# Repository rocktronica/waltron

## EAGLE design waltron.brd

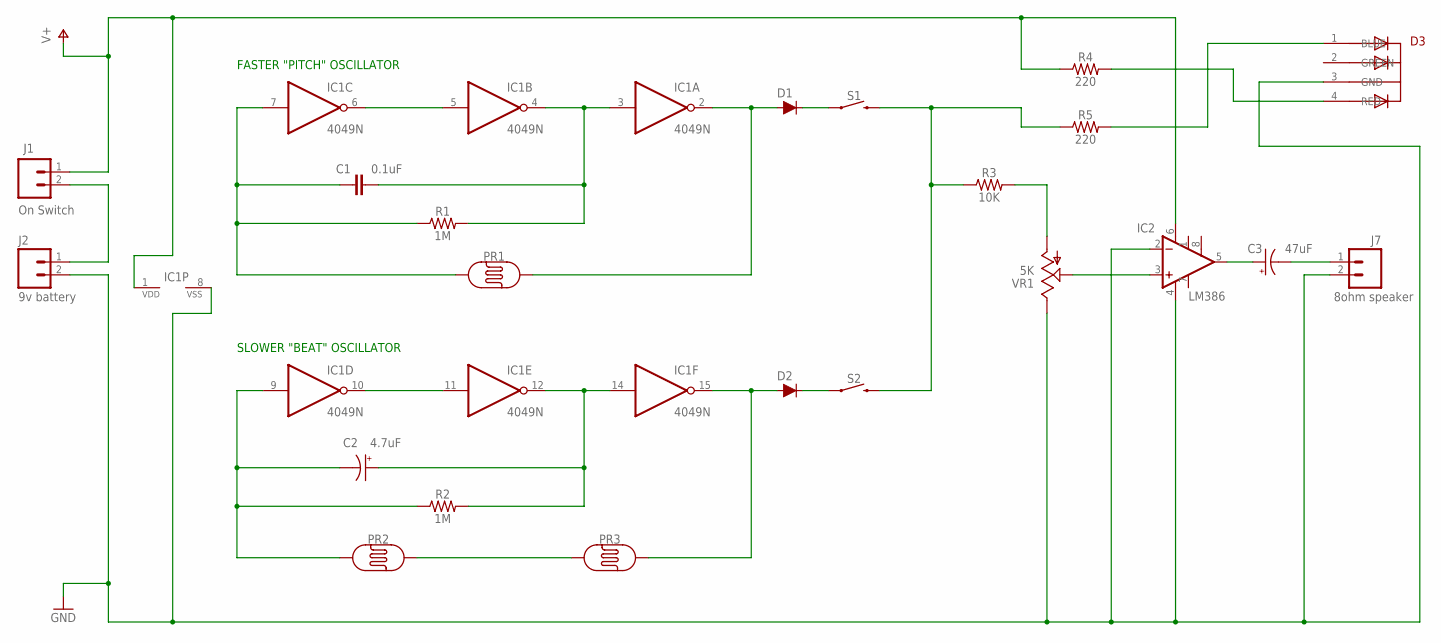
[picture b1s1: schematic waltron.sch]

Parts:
C1: 0.1uF; CAP-PTH-SMALL-KIT
C2: 4.7uF; CPOL-RADIAL-2.5MM-5MM
C3: 47uF; CPOL-RADIAL-2.5MM-5MM
D1, D2: DIODE-1N4148
D3: 5MMRGBLED; LED5MMRGB
IC1: 4049N; DIL16
IC2: LM386; DIP08
J1: On Switch; 1X02
J2: 9v battery; 1X02
J7: 8ohm speaker; 1X02
PR1, PR2, PR3: PHOTOCELLPTH-KIT; PHOTOCELL-KIT
R1, R2: 1M; AXIAL-0.3
R3: 10K; AXIAL-0.3
R4, R5: 220; AXIAL-0.3
S1, S2: MOMENTARY-SWITCH-SPST-PTH-6.0MM; TACTILE_SWITCH_PTH_6.0MM
VR1: 5K; TRIM_POT

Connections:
GND: D3.3 (GND), IC1.8 (VSS), IC2.2 (-IN), IC2.4 (V-), J2.2, J7.2, VR1.2 (E)
unnamed: IC1.5 (I), IC1.6 (O)
unnamed: C1.2, IC1.3 (I), IC1.4 (O), R1.P$2 (2)
unnamed: C1.1, IC1.7 (I), PR1.1, R1.P$1 (1)
unnamed: D1.A, IC1.2 (O), PR1.2
unnamed: C2.2 (-), IC1.9 (I), PR2.1, R2.P$1 (1)
unnamed: IC1.10 (O), IC1.11 (I)
unnamed: C2.1 (+), IC1.12 (O), IC1.14 (I), R2.P$2 (2)
unnamed: D2.A, IC1.15 (O), PR3.2
unnamed: D1.C, S1.1
unnamed: PR2.2, PR3.1
unnamed: D2.C, S2.1
unnamed: R3.P$1 (1), R5.P$1 (1), S1.3 (2), S2.3 (2)
unnamed: R3.P$2 (2), VR1.3 (A)
unnamed: C3.1 (+), IC2.5 (OUT)
unnamed: C3.2 (-), J7.1
unnamed: IC2.3 (+IN), VR1.1 (S)
unnamed: D3.1 (BLUE), R5.P$2 (2)
unnamed: D3.4 (RED), R4.P$2 (2)
unnamed: J1.2, J2.1
V+: IC1.1 (VDD), IC2.6 (V+), J1.1, R4.P$1 (1)

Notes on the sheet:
SLOWER "BEAT" OSCILLATOR
FASTER "PITCH" OSCILLATOR

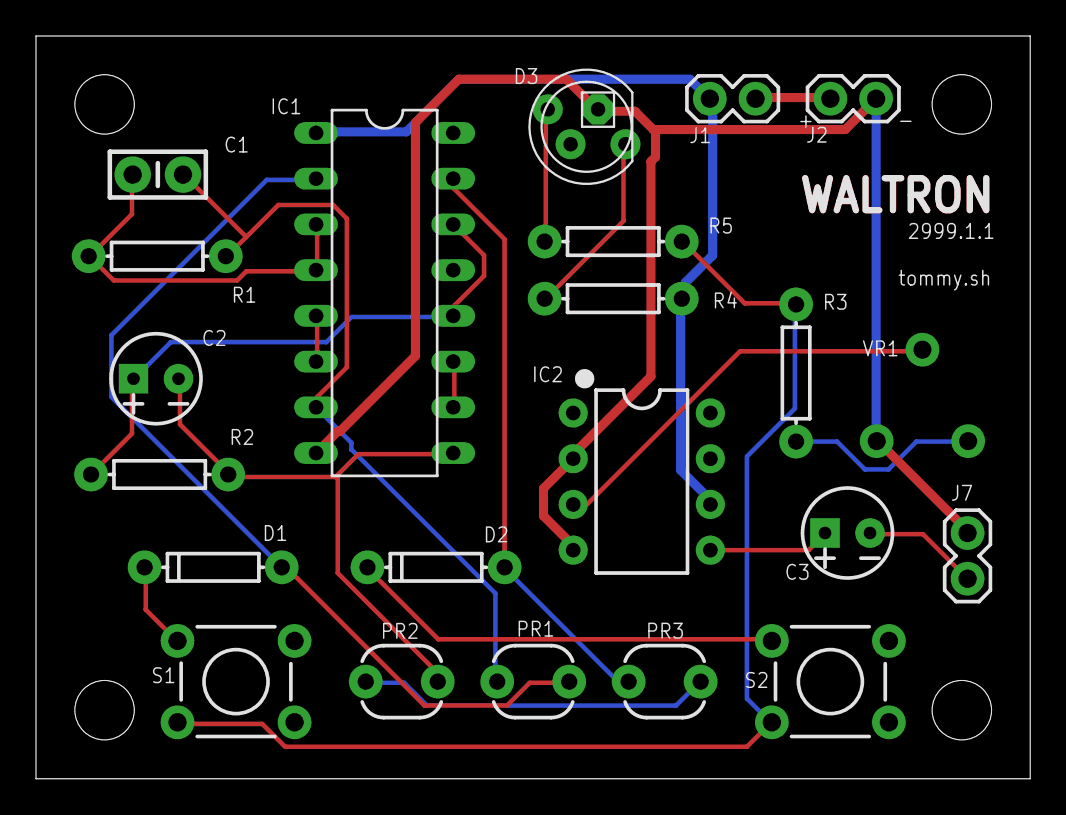
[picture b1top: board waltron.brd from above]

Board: 2 copper layers, 55.2 x 41.3 mm, 22 parts (1 on the bottom side), 21 nets.

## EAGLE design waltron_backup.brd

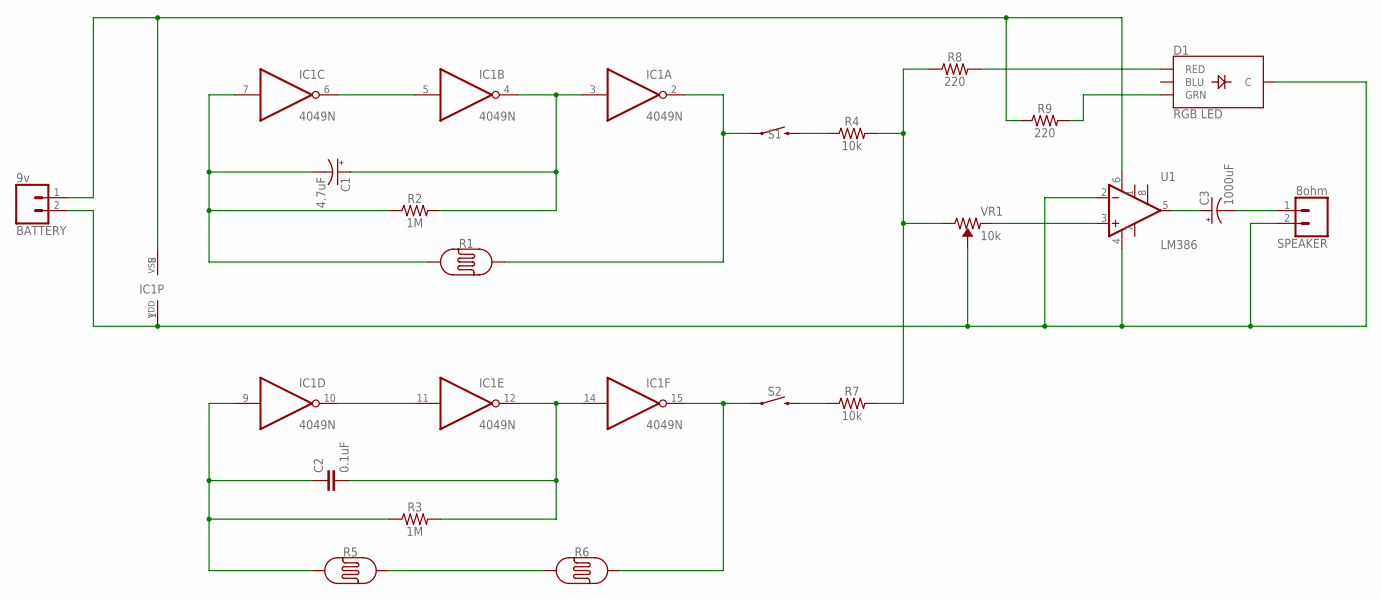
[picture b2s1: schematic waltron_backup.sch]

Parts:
BATTERY: 9v; 1X02
C1: 4.7uF; CPOL-RADIAL-2.5MM-5MM
C2: 0.1uF; CAP-PTH-SMALL-KIT
C3: 1000uF; CPOL-RADIAL-2.5MM-5MM
D1: RGB LED; LED-RGB-THRU
IC1: 4049N; DIL16
R1, R5, R6: PHOTOCELLPTH-KIT; PHOTOCELL-KIT
R2, R3: 1M; AXIAL-0.1
R4, R7: 10k; AXIAL-0.1
R8, R9: 220; AXIAL-0.1
S1, S2: MOMENTARY-SWITCH-SPST-PTH-6.0MM; TACTILE_SWITCH_PTH_6.0MM
SPEAKER: 8ohm; 1X02
U1: LM386; DIP08
VR1: 10k; TRIMPOT-PTH-3386U

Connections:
unnamed: IC1.5 (I), IC1.6 (O)
unnamed: C1.1 (+), IC1.3 (I), IC1.4 (O), R2.P$2 (2)
unnamed: C1.2 (-), IC1.7 (I), R1.1, R2.P$1 (1)
unnamed: IC1.2 (O), R1.2, S1.1
unnamed: C2.1, IC1.9 (I), R3.P$1 (1), R5.1
unnamed: IC1.10 (O), IC1.11 (I)
unnamed: C2.2, IC1.12 (O), IC1.14 (I), R3.P$2 (2)
unnamed: IC1.15 (O), R6.2, S2.1
unnamed: R4.P$1 (1), S1.3 (2)
unnamed: R5.2, R6.1
unnamed: R7.P$1 (1), S2.3 (2)
unnamed: R4.P$2 (2), R7.P$2 (2), R8.P$1 (1), VR1.3 (CW)
unnamed: U1.3 (+IN), VR1.1 (CCW)
unnamed: C3.1 (+), U1.5 (OUT)
unnamed: C3.2 (-), SPEAKER.1
unnamed: D1.1 (RED), R8.P$2 (2)
unnamed: D1.3 (GRN), R9.P$2 (2)
VDD: BATTERY.2, D1.2 (C), IC1.1 (VDD), SPEAKER.2, U1.2 (-IN), U1.4 (V-), VR1.2 (WIPER)
VSS: BATTERY.1, IC1.8 (VSS), R9.P$1 (1), U1.6 (V+)

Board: 2 copper layers, 20 parts (0 on the bottom side), 19 nets, no tracks yet.

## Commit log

2017-03-21 Belated init
2017-03-21 Remove lock
2017-03-21 Fix miswired volume pot
2017-03-21 Provide ground to D3
2017-03-21 Add battery lead labels
2017-03-21 Lay resistors flat, rip up routes
2017-03-22 Switch out trimmer
2017-03-22 Rearrange components, iterate version to 2999.1
2017-03-23 More rearrangement, separating out optional on-board parts
2017-03-24 New layout, routed
2017-03-24 Fix labels
2017-03-24 Re-routed, missing D3 GND
2017-03-24 Replaced D3 component w/ spaced leads
2017-03-24 Autorouted -- NO DRC ERRORS!
2017-03-25 Stack title text on top trace
2017-03-25 Optimize J connectors, reroute
2017-03-25 Move diodes above break
2017-03-25 Total rearrangement w/ guides, unrouted
2017-03-25 Routed
2017-03-25 Silk screen cleanup, ready to fab?
2017-04-13 Add stock ignore list
2017-04-13 Update schematic w/ 2999.1 concerns
    - use IC name for LM386 instead of U1
    - switch trim pot to model used in 4step
    - add switch connection
    - consistent J names for speaker and battery
2017-04-13 Rip up and lay out board
2017-04-14 Add mounting holes and swap out LED for mirrored version
2017-04-14 Remove headers, re-layout buttons+sensore, layout all
2017-04-14 Autoroute and finish 2999.1.1
2017-04-14 Put LED on top, re-route
2018-01-03 Add schematic
2018-01-03 Really ignore gitignore files
2018-01-03 Ignore and remove gerber files too
2018-01-05 Reverse volume knob rotation

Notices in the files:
parts and their libraries:
SparkFun-Capacitors: Licensing: Creative Commons ShareAlike 4.0 International - https://creativecommons.org/licenses/by-sa/4.0
